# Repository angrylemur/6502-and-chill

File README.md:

# 6502-and-chill
Laid-back tinkerings with 6502 computers.

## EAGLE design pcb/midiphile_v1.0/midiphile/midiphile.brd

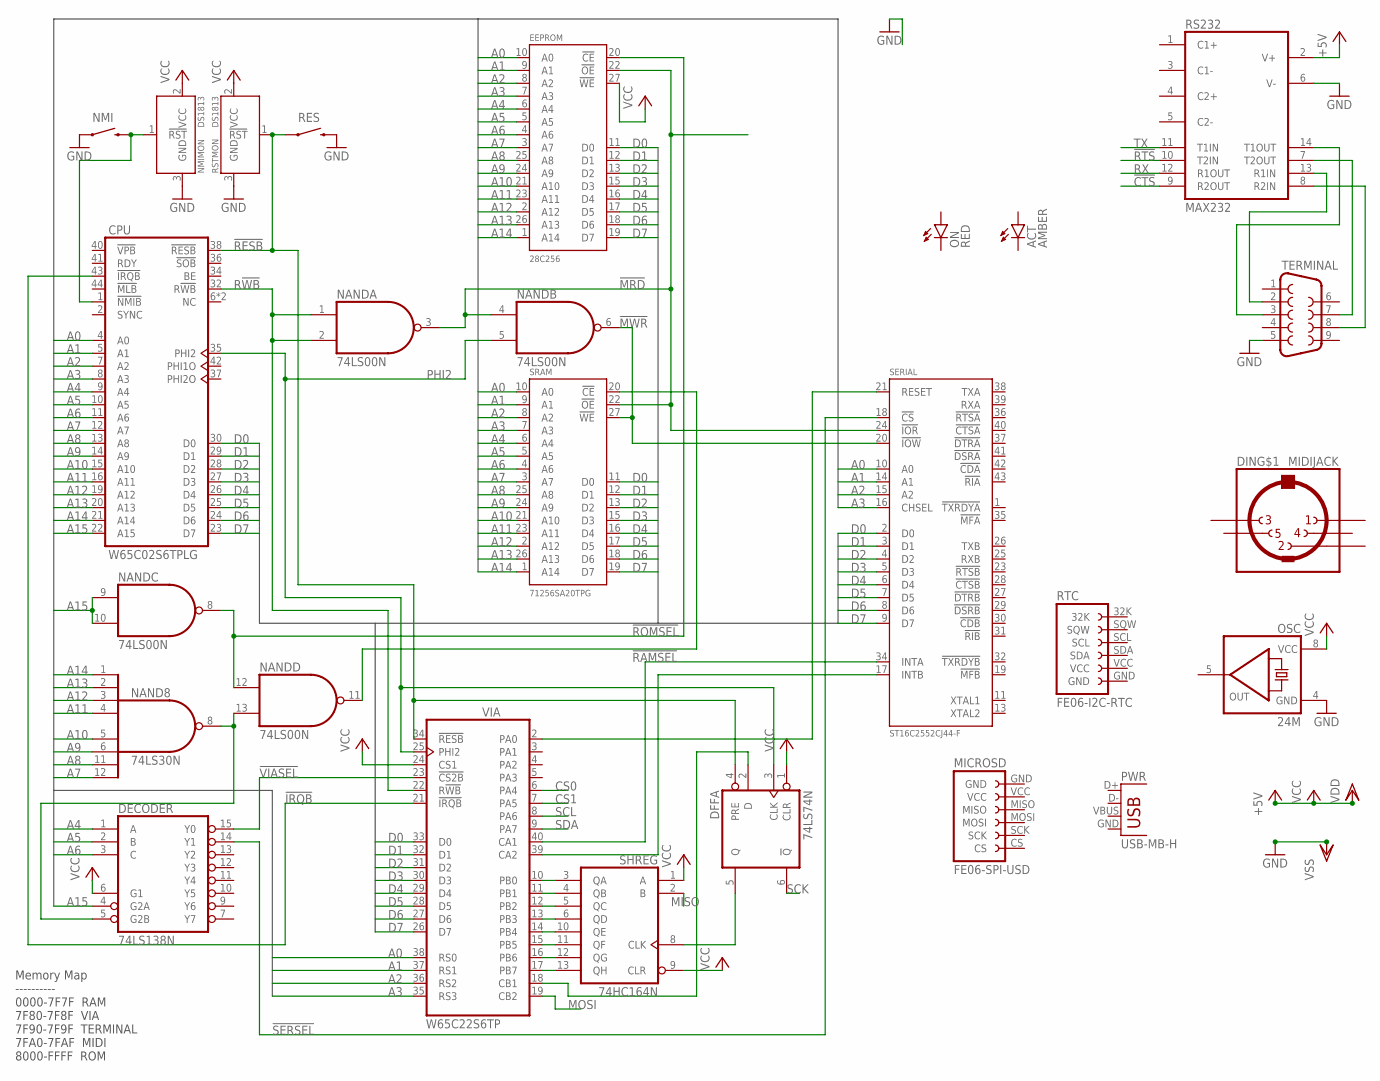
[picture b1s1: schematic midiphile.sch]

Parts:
ACT: AMBER; LED_RECT_2X5MM
CPU: W65C02S6TPLG; S44
DECODER: 74LS138N; DIL16
DFF: 74LS74N; DIL14
DIN: MIDIJACK; CP-2350
EEPROM: 28C256; DIL28
MICROSD: FE06-SPI-USD
NAND: 74LS00N; DIL14
NAND8: 74LS30N; DIL14
NMI: SWITCH-MOMENTARY-2PTH; TACTILE-PTH
NMIMON: DS1813; TO-92
ON: RED; LED_RECT_2X5MM
OSC: 24M; HALF_CAN_SOCKET
PWR: USB-MB-H
RES: SWITCH-MOMENTARY-2PTH; TACTILE-PTH
RS232: MAX232; DIL16
RSTMON: DS1813; TO-92
RTC: FE06-I2C-RTC
SERIAL: ST16C2552CJ44-F; S44
SHREG: 74HC164N; DIL14
SRAM: 71256SA20TPG; DIL28-3
TERMINAL: DB9MALE; DB9_MALE
VIA: W65C22S6TP; DIL40

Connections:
!CTS!: RS232.9 (R2OUT)
!IRQB!: CPU.43 (!IRQB), VIA.21 (!IRQB)
!MRD!: EEPROM.22 (!OE!), NAND.3 (O), NAND.4 (I0), SERIAL.24 (!IOR!), SRAM.22 (!OE!)
!MWR!: NAND.6 (O), SERIAL.20 (!IOW!), SRAM.27 (!WE!)
!RAMSEL!: NAND.11 (O), SRAM.20 (!CE!)
!RESB!: CPU.38 (!RESB), DFF.4 (PRE), RES.1, RSTMON.1 (!RST!), VIA.34 (!RESB)
!ROMSEL!: EEPROM.20 (!CE!), NAND.8 (O), NAND.12 (I0)
!RTS!: RS232.10 (T2IN)
!SERSEL!: DECODER.14 (Y1), SERIAL.18 (!CS!)
!VIASEL!: DECODER.15 (Y0), VIA.23 (!CS2B)
+5V: CPU.3 (VDD), CPU.31 (VDD), DECODER.16 (VCC), EEPROM.28 (VDD), NAND.14 (VCC), RS232.2 (V+), SERIAL.33 (VDD), SERIAL.44 (VDD), SHREG.14 (VCC), SRAM.28 (VDD)
A0: CPU.4 (A0), EEPROM.10 (A0), SERIAL.10 (A0), SRAM.10 (A0), VIA.38 (RS0)
A1: CPU.5 (A1), EEPROM.9 (A1), SERIAL.14 (A1), SRAM.9 (A1), VIA.37 (RS1)
A2: CPU.7 (A2), EEPROM.8 (A2), SERIAL.15 (A2), SRAM.8 (A2), VIA.36 (RS2)
A3: CPU.8 (A3), EEPROM.7 (A3), SERIAL.16 (CHSEL), SRAM.7 (A3), VIA.35 (RS3)
A4: CPU.9 (A4), DECODER.1 (A), EEPROM.6 (A4), SRAM.6 (A4)
A5: CPU.10 (A5), DECODER.2 (B), EEPROM.5 (A5), SRAM.5 (A5)
A6: CPU.11 (A6), DECODER.3 (C), EEPROM.4 (A6), SRAM.4 (A6)
A7: CPU.12 (A7), EEPROM.3 (A7), NAND8.12 (I7), SRAM.3 (A7)
A8: CPU.13 (A8), EEPROM.25 (A8), NAND8.11 (I6), SRAM.25 (A8)
A9: CPU.14 (A9), EEPROM.24 (A9), NAND8.6 (I5), SRAM.24 (A9)
A10: CPU.15 (A10), EEPROM.21 (A10), NAND8.5 (I4), SRAM.21 (A10)
A11: CPU.16 (A11), EEPROM.23 (A11), NAND8.4 (I3), SRAM.23 (A11)
A12: CPU.19 (A12), EEPROM.2 (A12), NAND8.3 (I2), SRAM.2 (A12)
A13: CPU.20 (A13), EEPROM.26 (A13), NAND8.2 (I1), SRAM.26 (A13)
A14: CPU.21 (A14), EEPROM.1 (A14), NAND8.1 (I0), SRAM.1 (A14)
A15: CPU.22 (A15), DECODER.4 (G2A), NAND.9 (I0), NAND.10 (I1)
CS0: VIA.6 (PA4)
CS1: VIA.7 (PA5)
D0: CPU.30 (D0), EEPROM.11 (D0), SERIAL.2 (D0), SRAM.11 (D0), VIA.33 (D0)
D1: CPU.29 (D1), EEPROM.12 (D1), SERIAL.3 (D1), SRAM.12 (D1), VIA.32 (D1)
D2: CPU.28 (D2), EEPROM.13 (D2), SERIAL.4 (D2), SRAM.13 (D2), VIA.31 (D2)
D3: CPU.27 (D3), EEPROM.15 (D3), SERIAL.5 (D3), SRAM.15 (D3), VIA.30 (D3)
D4: CPU.26 (D4), EEPROM.16 (D4), SERIAL.6 (D4), SRAM.16 (D4), VIA.29 (D4)
D5: CPU.25 (D5), EEPROM.17 (D5), SERIAL.7 (D5), SRAM.17 (D5), VIA.28 (D5)
D6: CPU.24 (D6), EEPROM.18 (D6), SERIAL.8 (D6), SRAM.18 (D6), VIA.27 (D6)
D7: CPU.23 (D7), EEPROM.19 (D7), SERIAL.9 (D7), SRAM.19 (D7), VIA.26 (D7)
GND: CPU.17 (VSS), CPU.18 (VSS), CPU.39 (VSS), DECODER.8 (GND), DFF.7 (GND), EEPROM.14 (VSS), NAND.7 (GND), NAND8.7 (GND), NMI.1, NMIMON.3 (GND), OSC.4 (GND), RES.3 (2), RS232.6 (V-), RS232.15 (GND), RSTMON.3 (GND), SERIAL.12 (VSS), SERIAL.22 (VSS), SHREG.7 (GND), SRAM.14 (VSS), TERMINAL.5
MISO: SHREG.2 (B)
MOSI: VIA.19 (CB2)
unnamed: CPU.1 (!NMIB), NMI.3 (2), NMIMON.1 (!RST!)
unnamed: DECODER.5 (G2B), NAND.13 (I1), NAND8.8 (O)
unnamed: SERIAL.17 (INTB), VIA.39 (CA2)
unnamed: SERIAL.34 (INTA), VIA.40 (CA1)
unnamed: SERIAL.21 (RESET), VIA.2 (PA0)
unnamed: SHREG.3 (QA), VIA.10 (PB0)
unnamed: SHREG.4 (QB), VIA.11 (PB1)
unnamed: SHREG.5 (QC), VIA.12 (PB2)
unnamed: SHREG.6 (QD), VIA.13 (PB3)
unnamed: SHREG.10 (QE), VIA.14 (PB4)
unnamed: SHREG.11 (QF), VIA.15 (PB5)
unnamed: SHREG.12 (QG), VIA.16 (PB6)
unnamed: SHREG.13 (QH), VIA.17 (PB7)
unnamed: DFF.2 (D), VIA.18 (CB1)
unnamed: DFF.5 (Q), SHREG.8 (CLK)
unnamed: RS232.14 (T1OUT), TERMINAL.3
unnamed: RS232.13 (R1IN), TERMINAL.2
unnamed: RS232.7 (T2OUT), TERMINAL.7
unnamed: RS232.8 (R2IN), TERMINAL.8
PHI2: CPU.35 (PHI2), DFF.3 (CLK), NAND.5 (I1), VIA.25 (PHI2)
R!WB!: CPU.32 (R!WB), NAND.1 (I0), NAND.2 (I1), VIA.22 (R!WB)
RX: RS232.12 (R1OUT)
SCK: DFF.6 (!Q)
SCL: VIA.8 (PA6)
SDA: VIA.9 (PA7)
TX: RS232.11 (T1IN)
VCC: DECODER.6 (G1), DFF.1 (CLR), DFF.14 (VCC), EEPROM.27 (!WE!), NAND8.14 (VCC), NMIMON.2 (VCC), OSC.8 (VCC), RS232.16 (VCC), RSTMON.2 (VCC), SHREG.1 (A), SHREG.9 (CLR), VIA.24 (CS1)
VDD: EEPROM.28 (VDD), VIA.20 (VDD)
VSS: EEPROM.14 (VSS), VIA.1 (VSS)

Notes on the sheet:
Memory Map ---------- 0000-7F7F RAM 7F80-7F8F VIA 7F90-7F9F TERMINAL 7FA0-7FAF MIDI 8000-FFFF ROM

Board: 2 copper layers, 23 parts (0 on the bottom side), 58 nets, no tracks yet.

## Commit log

2022-06-24 Establish midiphile eagle project
2022-07-02 Add PLCC packages for 65c02 and 16550; roughly lay out ICs on board
2022-07-03 Add oscillators, reset and nmi, and thinner sram
2022-07-08 Add 16C2552, expansion headers, rectangular LEDs

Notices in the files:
parts and their libraries:
SparkFun-Connectors: Licensing: Creative Commons ShareAlike 4.0 International - https://creativecommons.org/licenses/by-sa/4.0
